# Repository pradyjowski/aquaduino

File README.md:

aquaduino
=========

Arduino based aquarium controller measuring Ph and temperature, LCD-UI + RTC + datalogging SD

Achieved:
- LCD display over i2c interface
- Functional 3-button menu in English and Polish
- Ph probe reading with calibration code
- EEPROM save of Ph calibration
- Temperature reading [DS18B20]
- Data and clock [DS1307]
- SD card logging

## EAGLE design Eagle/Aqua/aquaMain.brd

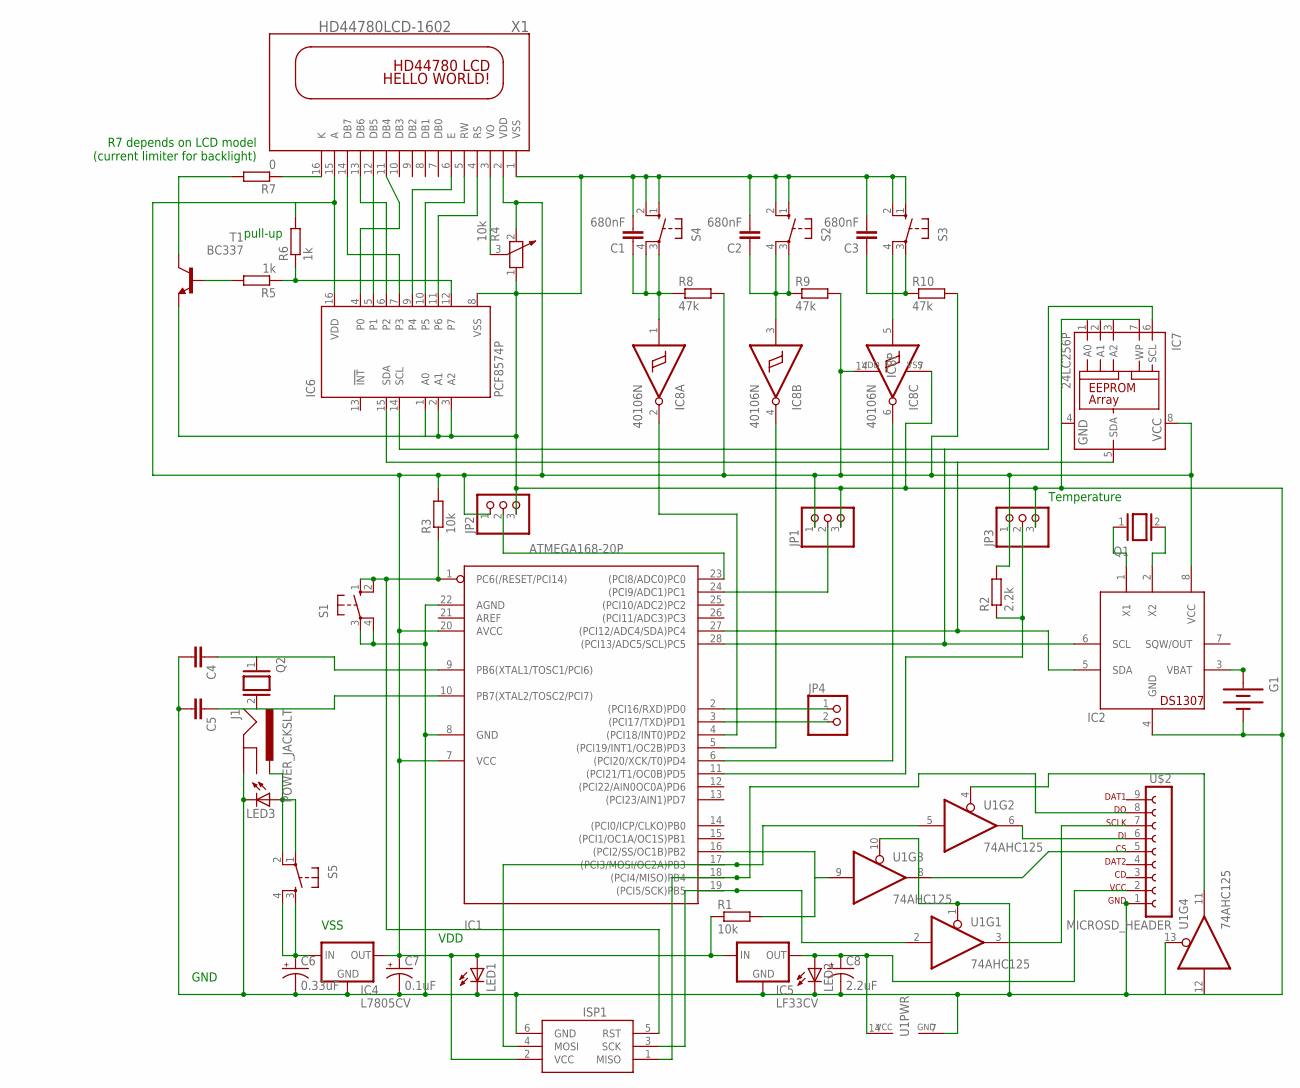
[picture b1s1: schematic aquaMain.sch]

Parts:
C1, C2, C3: 680nF; C050-050X075
C4, C5: C-EU025-024X044; C025-024X044
C6: 0.33uF; E5-6
C7: 0.1uF; E5-6
C8: 2.2uF; E5-6
G1: BATTERY20PTH; BATTCOM_20MM_PTH
IC1: ATMEGA168-20P; DIL28-3
IC2: DS1307; DIL08
IC4: L7805CV; TO220
IC5: LF33CV; TO220
IC6: PCF8574P; DIL16
IC7: 24LC256P; DIL8
IC8: 40106N; DIL14
ISP1: AVRISP-6; AVRISP
J1: POWER_JACKSLT; POWER_JACK_SLOT
JP1, JP2, JP3: PINHD-1X3; 1X03
JP4: PINHD-1X2; 1X02
LED1, LED2, LED3: LED3MM
Q1, Q2: XTAL/S; QS
R1, R3: 10k; 0204/7
R2: 2.2k; 0204/7
R4: 10k; PT-10
R5, R6: 1k; 0204/5
R7: 0; 0204/5
R8, R9, R10: 47k; 0204/5
S1, S2, S3, S4: 40-XX-ROUND; B3F-40XX-ROUND
S5: TAC_SWITCHPTH; TACTILE-PTH
T1: BC337; TO92
U1: 74AHC125; DIP14
U$2: MICROSD_HEADER; 9PINH
X1: HD44780LCD-1602; LCD1602

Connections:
unnamed: IC1.23 ((PCI8/ADC0)PC0), JP2.2
unnamed: IC1.5 ((PCI19/INT1/OC2B)PD3), IC8.4 (O)
unnamed: IC2.1 (X1), Q1.1
unnamed: IC2.2 (X2), Q1.2
unnamed: G1.1 (+), IC2.3 (VBAT)
unnamed: IC1.11 ((PCI21/T1/OC0B)PD5), JP3.2, R2.1
unnamed: IC1.28 ((PCI13/ADC5/SCL)PC5), IC2.6 (SCL), IC6.14 (SCL), IC7.6 (SCL)
unnamed: IC1.4 ((PCI18/INT0)PD2), IC8.2 (O)
unnamed: IC1.6 ((PCI20/XCK/T0)PD4), IC8.6 (O)
unnamed: C4.1, IC1.9 (PB6(XTAL1/TOSC1/PCI6)), Q2.1
unnamed: C5.1, IC1.10 (PB7(XTAL2/TOSC2/PCI7)), Q2.2
unnamed: IC1.18 ((PCI4/MISO)PB4), ISP1.1 (MISO), U$2.8
unnamed: IC1.17 ((PCI3/MOSI/OC2A)PB3), ISP1.4 (MOSI), U1.5 (I)
unnamed: IC1.16 ((PCI2/SS/OC1B)PB2), R1.2, U1.9 (I)
unnamed: IC1.19 ((PCI5/SCK)PB5), ISP1.3 (SCK), U1.2 (I)
unnamed: U1.3 (O), U$2.7
unnamed: U1.8 (O), U$2.5
unnamed: U1.6 (O), U$2.6
unnamed: IC1.1 (PC6(/RESET/PCI14)), ISP1.5 (RST), R3.1, S1.1 (S), S1.2 (S1)
unnamed: IC1.27 ((PCI12/ADC4/SDA)PC4), IC2.5 (SDA), IC6.15 (SDA), IC7.5 (SDA)
unnamed: C8.+, IC5.VOUT (OUT), LED2.A, U1.14 (VCC), U$2.2
unnamed: R4.3, X1.3 (VO)
unnamed: IC1.24 ((PCI9/ADC1)PC1), JP1.2
unnamed: C7.+, IC1.7 (VCC), IC1.20 (AVCC), IC2.8 (VCC), IC4.VOUT (OUT), IC5.VIN (IN), IC6.16 (VDD), IC7.8 (VCC), IC8.14 (VDD), ISP1.2 (VCC), JP1.1, JP2.1, JP3.1, LED1.A, R1.1, R2.2, R3.2, R4.2, R6.2, R8.2, R9.2, R10.2, X1.2 (VDD), X1.15 (A)
unnamed: J1.PWR, LED3.A, S5.1, S5.2
unnamed: IC6.4 (P0), X1.11 (DB4)
unnamed: IC6.5 (P1), X1.12 (DB5)
unnamed: IC6.6 (P2), X1.13 (DB6)
unnamed: IC6.7 (P3), X1.14 (DB7)
unnamed: IC6.9 (P4), X1.6 (E)
unnamed: IC6.10 (P5), X1.5 (RW)
unnamed: IC6.11 (P6), X1.4 (RS)
unnamed: IC6.12 (P7), R5.1, R6.1
unnamed: R5.2, T1.2 (B)
unnamed: R7.1, X1.16 (K)
unnamed: R7.2, T1.3 (C)
unnamed: C1.1, IC8.1 (I), R8.1, S4.3, S4.4 (P1)
unnamed: C2.1, IC8.3 (I), R9.1, S2.3, S2.4 (P1)
unnamed: C3.1, IC8.5 (I), R10.1, S3.3, S3.4 (P1)
unnamed: C6.+, IC4.VIN (IN), S5.3, S5.4
unnamed: IC1.2 ((PCI16/RXD)PD0), JP4.1
unnamed: IC1.3 ((PCI17/TXD)PD1), JP4.2
unnamed: U1.4 (OE), U1.11 (O)
VSS: C1.2, C2.2, C3.2, C4.2, C5.2, C6.-, C7.-, C8.-, G1.2 (-), IC1.8 (GND), IC1.22 (AGND), IC2.4 (GND), IC4.GND, IC5.GND, IC6.1 (A0), IC6.2 (A1), IC6.3 (A2), IC6.8 (VSS), IC7.1 (A0), IC7.2 (A1), IC7.3 (A2), IC7.4 (GND), IC7.7 (WP), IC8.7 (VSS), ISP1.6 (GND), J1.GND@2 (GND), JP1.3, JP2.3, JP3.3, LED1.K (C), LED2.K (C), LED3.K (C), R4.1, S1.3, S1.4 (P1), S2.1 (S), S2.2 (S1), S3.1 (S), S3.2 (S1), S4.1 (S), S4.2 (S1), T1.1 (E), U1.1 (OE), U1.7 (GND), U1.10 (OE), U1.12 (I), U1.13 (OE), U$2.1, X1.1 (VSS)

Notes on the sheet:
Temperature
R7 depends on LCD model (current limiter for backlight)
pull-up
GND
VSS
VDD

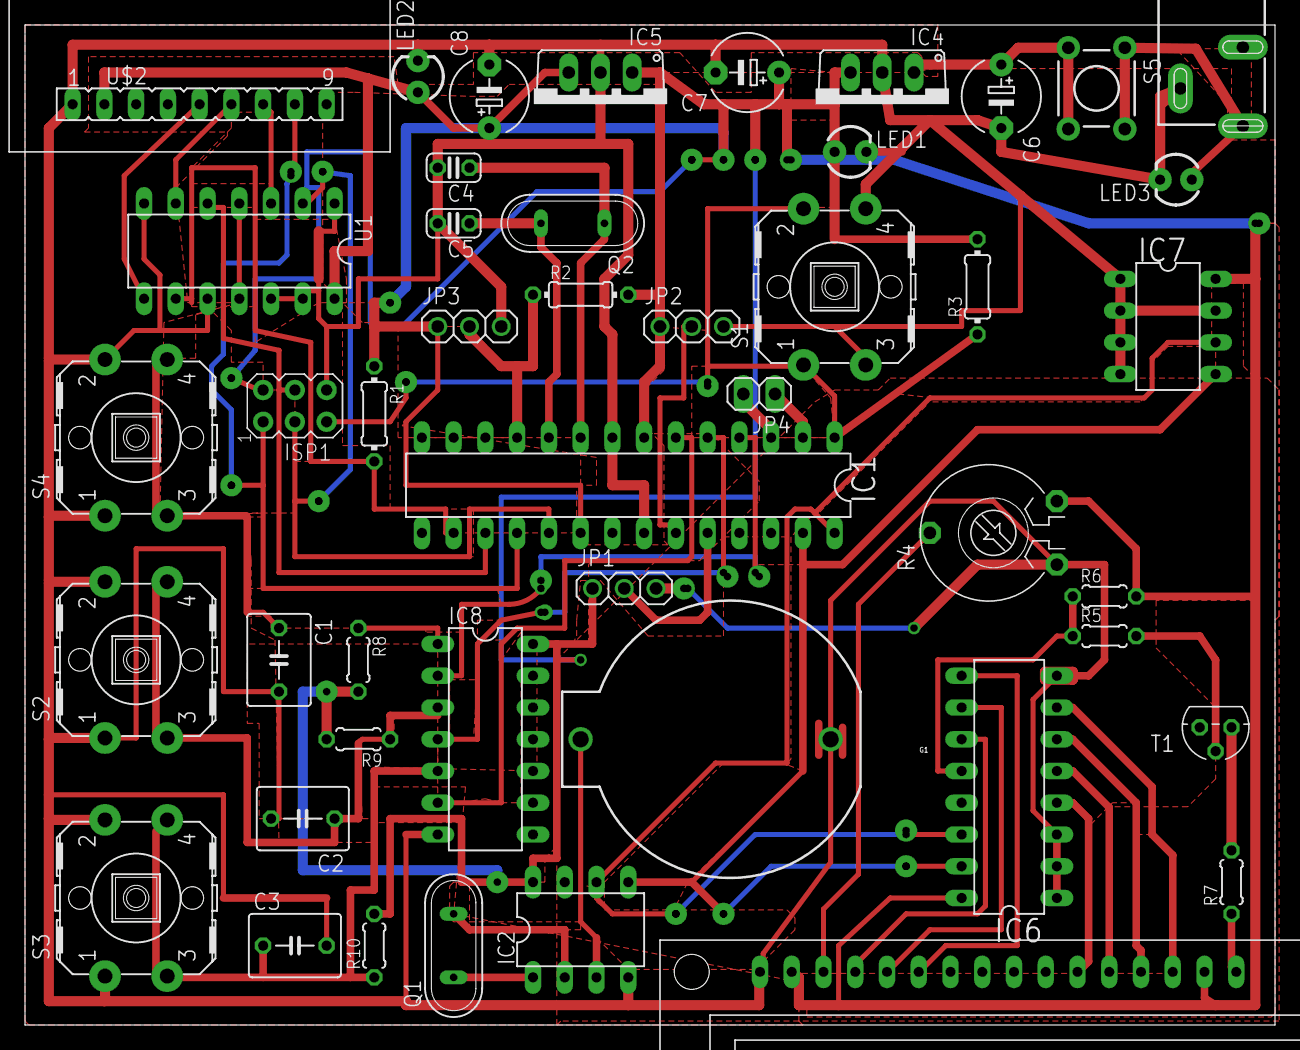
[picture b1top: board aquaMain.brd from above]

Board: 2 copper layers, 100.0 x 80.0 mm, 46 parts (0 on the bottom side), 44 nets.

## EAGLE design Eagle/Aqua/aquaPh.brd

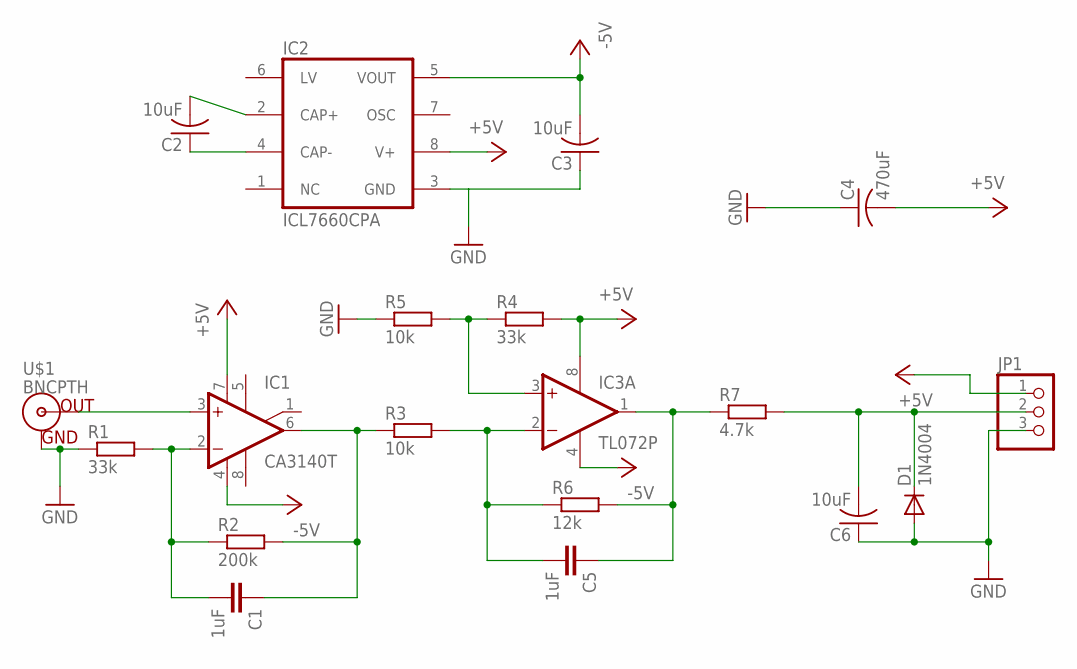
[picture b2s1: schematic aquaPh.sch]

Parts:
C1, C5: 1uF; C050-035X075
C2, C3, C6: 10uF; C075-042X103
C4: 470uF; C075-042X103
D1: 1N4004; DO41-10
IC1: CA3140T; TO99
IC2: ICL7660CPA; DIL08
IC3: TL072P; DIL08
JP1: PINHD-1X3; 1X03
R1, R4: 33k; 0204/5
R2: 200k; 0204/5
R3, R5: 10k; 0204/5
R6: 12k; 0204/5
R7: 4.7k; 0204/5
U$1: BNCPTH; BNC

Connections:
-5V: C3.2, IC1.4 (V-), IC2.5 (VOUT), IC3.4 (V-)
GND: C3.1, C4.1, C6.1, D1.A, IC2.3 (GND), JP1.3, R1.1, R5.1, U$1.GND
unnamed: IC1.3 (+IN), U$1.S (OUT)
unnamed: C1.2, IC1.2 (-IN), R1.2, R2.1
unnamed: C2.1, IC2.4 (CAP-)
unnamed: C2.2, IC2.2 (CAP+)
unnamed: C1.1, IC1.6 (OUT), R2.2, R3.1
unnamed: C5.2, IC3.2 (-IN), R3.2, R6.1
unnamed: IC3.3 (+IN), R4.1, R5.2
unnamed: C5.1, IC3.1 (OUT), R6.2, R7.1
unnamed: C6.2, D1.C, JP1.2, R7.2
VCC: C4.2, IC1.7 (V+), IC2.8 (V+), IC3.8 (V+), JP1.1, R4.2

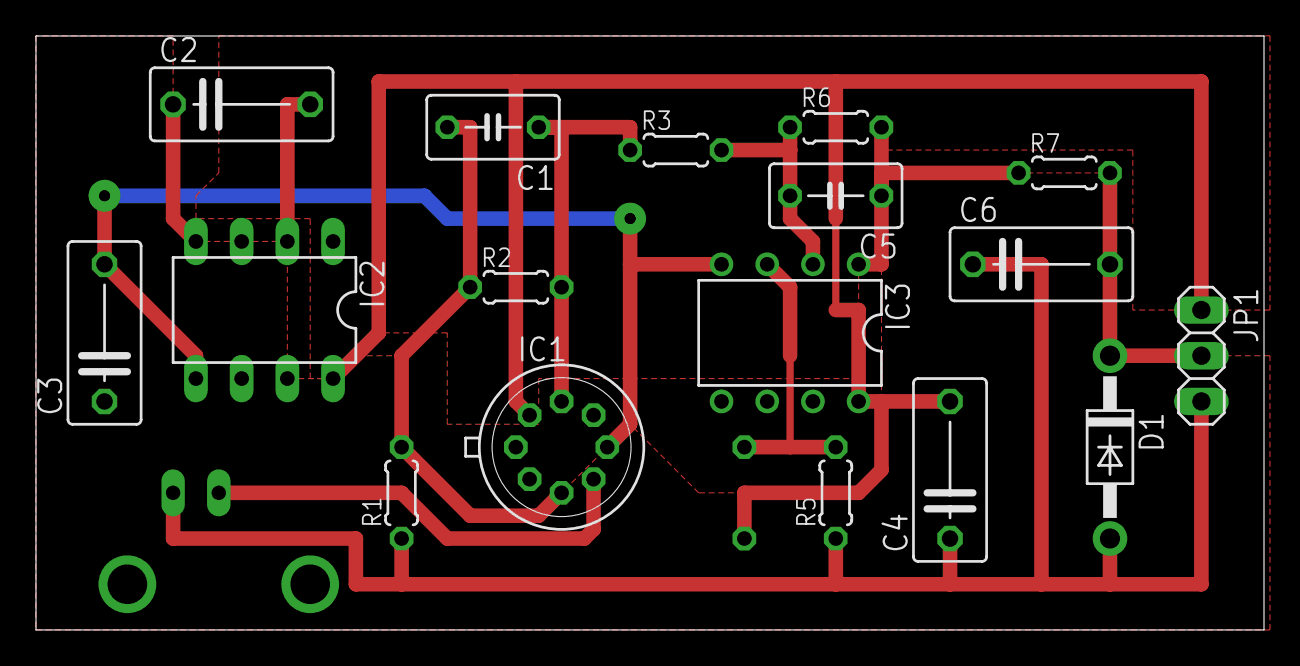
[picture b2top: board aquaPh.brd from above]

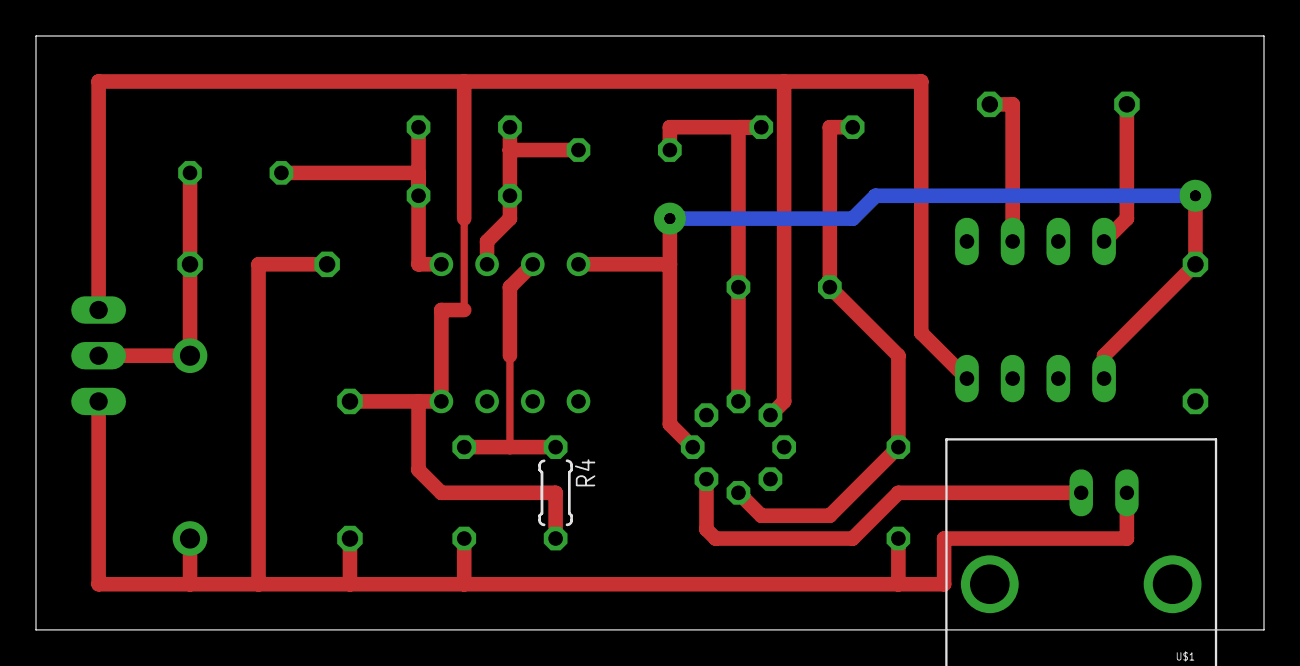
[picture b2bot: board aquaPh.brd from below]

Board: 2 copper layers, 68.2 x 33.0 mm, 19 parts (2 on the bottom side), 12 nets.

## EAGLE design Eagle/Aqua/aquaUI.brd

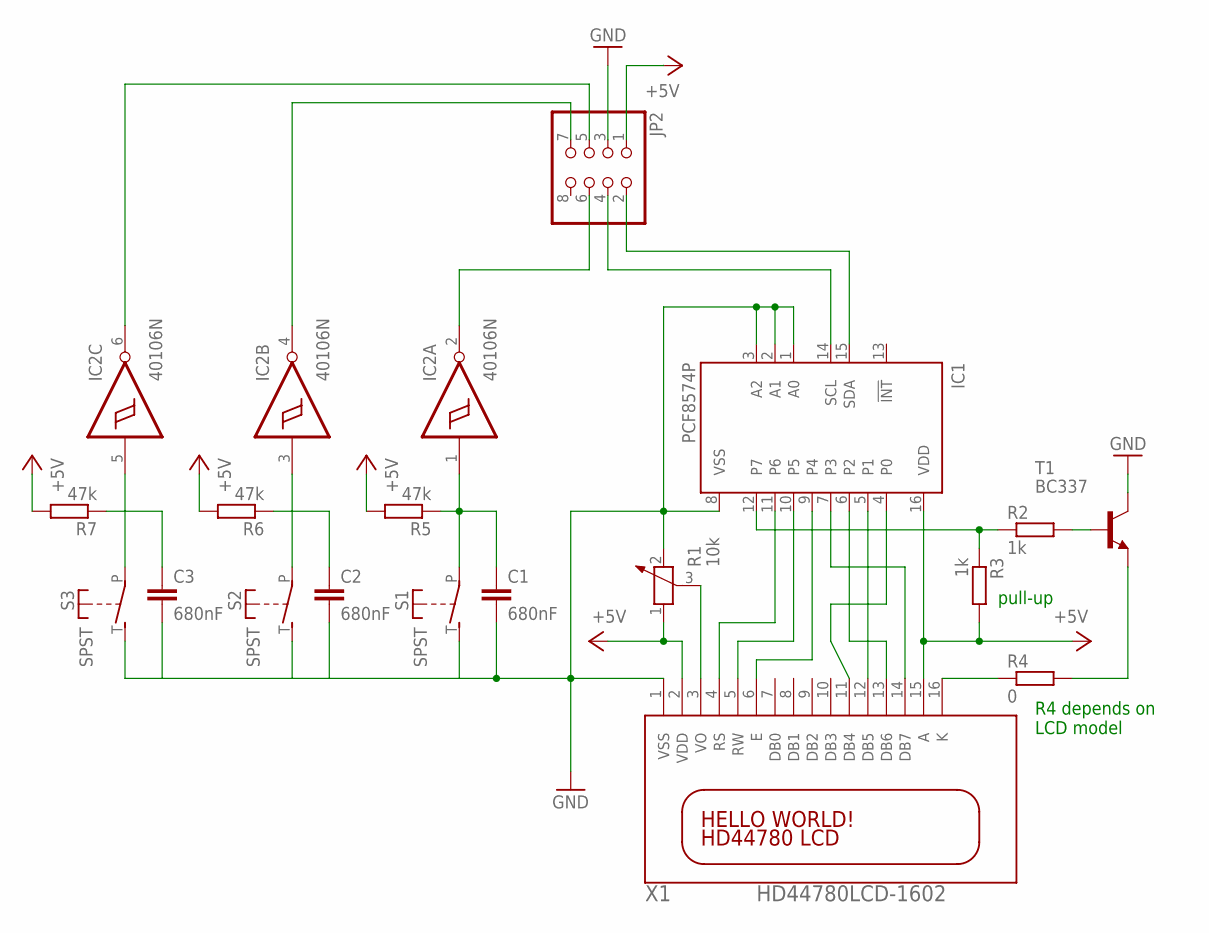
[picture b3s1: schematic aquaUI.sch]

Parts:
C1, C2, C3: 680nF; C050-050X075
IC1: PCF8574P; DIL16
IC2: 40106N; DIL14
JP2: PINHD-2X4; 2X04
R1: 10k; PT-10
R2, R3: 1k; 0204/5
R4: 0; 0204/5
R5, R6, R7: 47k; 0204/5
S1, S2, S3: SPST; JUDCOSPST
T1: BC337; TO92
X1: HD44780LCD-1602; LCD1602

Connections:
+5V: IC1.16 (VDD), IC2.14 (VDD), JP2.1, R1.1, R3.2, R5.2, R6.2, R7.2, X1.2 (VDD), X1.15 (A)
GND: C1.2, C2.2, C3.2, IC1.1 (A0), IC1.2 (A1), IC1.3 (A2), IC1.8 (VSS), IC2.7 (VSS), JP2.3, R1.2, S1.T (S), S2.T (S), S3.T (S), T1.3 (C), X1.1 (VSS)
unnamed: IC1.15 (SDA), JP2.2
unnamed: IC1.14 (SCL), JP2.4
unnamed: R1.3, X1.3 (VO)
unnamed: IC1.4 (P0), X1.11 (DB4)
unnamed: IC1.5 (P1), X1.12 (DB5)
unnamed: IC1.6 (P2), X1.13 (DB6)
unnamed: IC1.7 (P3), X1.14 (DB7)
unnamed: IC1.9 (P4), X1.6 (E)
unnamed: IC1.10 (P5), X1.5 (RW)
unnamed: IC1.11 (P6), X1.4 (RS)
unnamed: IC1.12 (P7), R2.1, R3.1
unnamed: R2.2, T1.2 (B)
unnamed: R4.1, X1.16 (K)
unnamed: R4.2, T1.1 (E)
unnamed: C1.1, IC2.1 (I), R5.1, S1.P
unnamed: C2.1, IC2.3 (I), R6.1, S2.P
unnamed: C3.1, IC2.5 (I), R7.1, S3.P
unnamed: IC2.2 (O), JP2.6
unnamed: IC2.6 (O), JP2.5
unnamed: IC2.4 (O), JP2.7

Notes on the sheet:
R4 depends on LCD model
pull-up

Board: 2 copper layers, 18 parts (1 on the bottom side), 22 nets, no tracks yet.

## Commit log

2014-02-16 Initial commit of arduino program - Basic reading and dummy conversion of ph probe, OneWire temperature & DS1307 RTC; display on lcd connected through i2c
2014-02-16 Added missing dummy calibration points
2014-02-17 Preliminary board design (no PCB routing yet)
2014-02-17 Added calibration function / UI and saving to EEPROM No-delay counting down waiting for button press
2014-03-24 Finished experimental board design Added PCB converted Arduino NANO <-> DIP 28
2014-03-24 Filled empty spaces with copper (faster eatching) Redone ArduinoNANO to DIP28 PCB to a single-side version Added V1 printout image
2014-05-17 Big update Many important fixes dictated by 1st prototype
2014-05-20 - important fix to SD wiring (not implemented in PCB yet) - SD logging function in arduino project
2015-01-09 Final project commit: - prototype proven to working continously for 4 months as of 1/8/15 - added pictures - [1/5/15] improvement - decrease R2 to 2.2kOhm, improved SNR from DS18B20 - project finished
    Achieved:
    - LCD display over i2c interface
    - Functional 3-button menu English and Polish
    - Ph probe reading with calibration code
    - EEPROM save of Ph calibration
    - Temperature reading [DS18B20]

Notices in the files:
parts and their libraries:
SparkFun-Connectors: Licensing: Creative Commons ShareAlike 4.0 International - https://creativecommons.org/licenses/by-sa/4.0
